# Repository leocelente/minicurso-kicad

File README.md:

# minicurso-kicad
Output of a half-day course on KiCAD

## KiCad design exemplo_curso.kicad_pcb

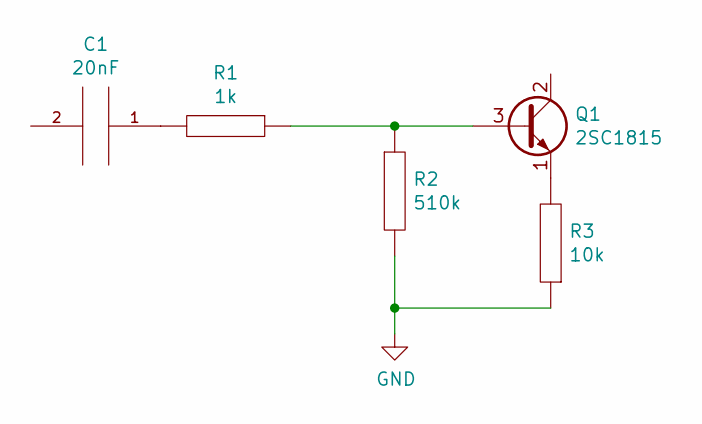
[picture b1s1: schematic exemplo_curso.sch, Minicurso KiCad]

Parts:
C1: 20nF; C_Disc_D3.0mm_W1.6mm_P2.50mm
Q1: 2SC1815; TO-92_Inline
R1: 1k; R_Axial_DIN0207_L6.3mm_D2.5mm_P10.16mm_Horizontal
R2: 510k; R_Axial_DIN0207_L6.3mm_D2.5mm_P10.16mm_Horizontal
R3: 10k; R_Axial_DIN0207_L6.3mm_D2.5mm_P10.16mm_Horizontal

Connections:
GND: R2.2, R3.1
unnamed: C1.1, R1.2
unnamed: Q1.1 (E), R3.2
unnamed: Q1.3 (B), R1.1, R2.1

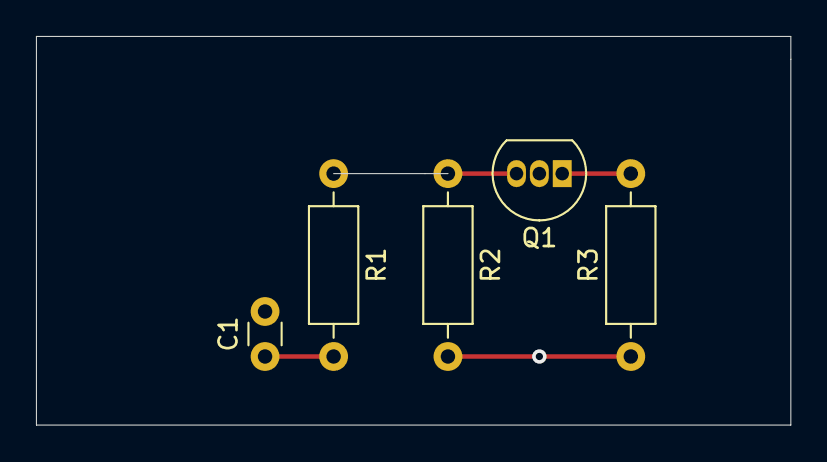
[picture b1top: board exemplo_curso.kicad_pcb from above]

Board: 2 copper layers, 41.9 x 21.6 mm, 5 parts (0 on the bottom side), 4 nets.

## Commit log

2019-10-01 Initial Commit
    A third of the schematic.
2019-10-01 Cap unit added
2019-10-01 Added footprints
2019-10-01 last commit
